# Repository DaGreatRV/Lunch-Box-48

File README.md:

Lunch-Box-48
============

A small Avalon based miner

See the thread on bitcointalk/simple machines forum:
https://bitcointalk.org/index.php?topic=219489.0

Terms of use:
I will not take any responsibility for the use, misuse and/or functionality of the work done in this repository.
You are allowed to use and modify the designs in this repository, please do credit me.
If you modify the design(s), please share them and credit me.
You are allowed to use my designs to build a device for private and/or prototype purposes.
If you would like to use this work for commercial purposes(i.e. manufactor and/or selling it), contact me and we can discuss some form of compensation.

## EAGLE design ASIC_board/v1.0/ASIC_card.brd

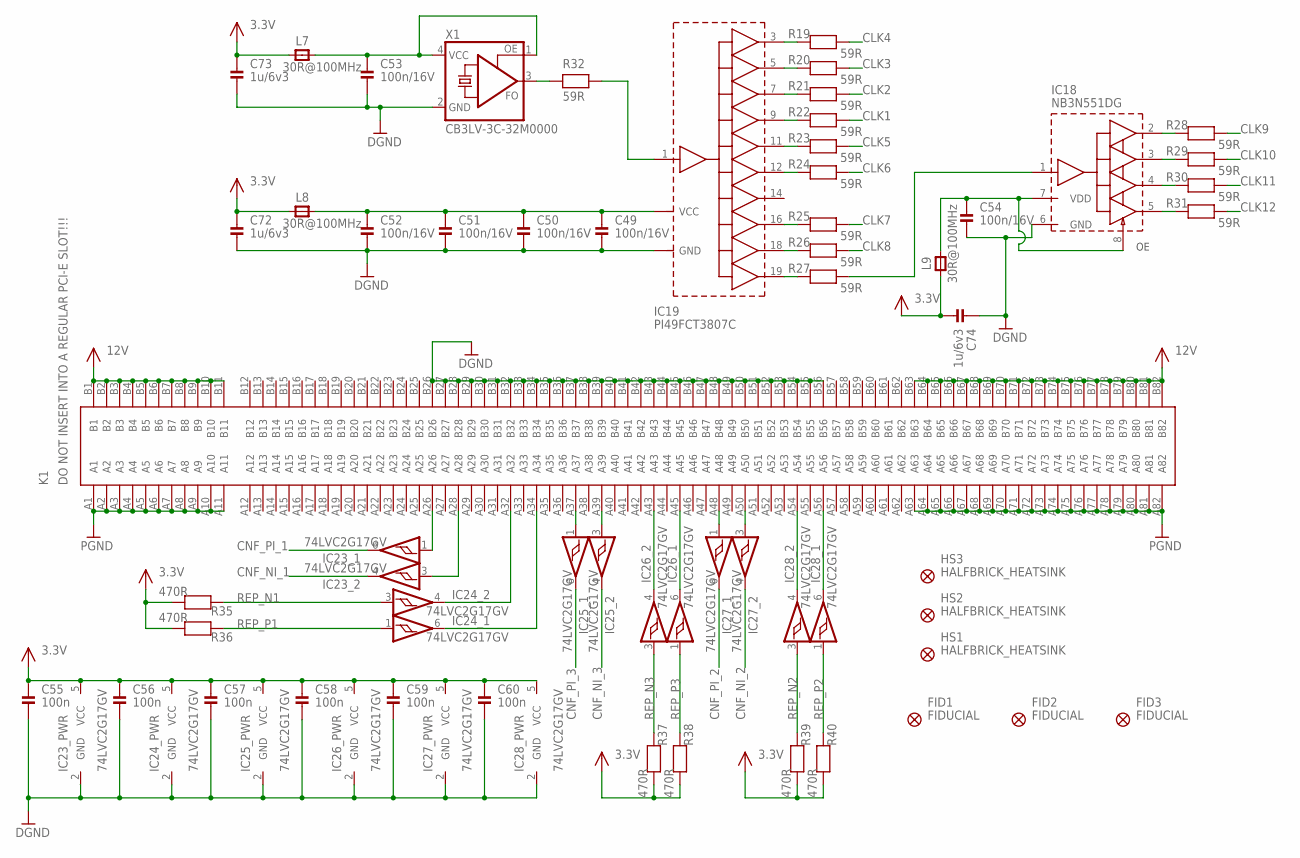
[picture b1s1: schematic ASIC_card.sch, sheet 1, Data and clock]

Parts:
C49, C50, C51, C52, C53, C54: 100n/16V; 0402
C55, C56, C57, C58, C59, C60: 100n; 0603
C72, C73, C74: 1u/6v3; 0402
FID1, FID2, FID3: FIDUCIAL; FID_1X2,5
HS1, HS2, HS3: HALFBRICK_HEATSINK; 1/2_BRICK_HEATSINK
IC18: NB3N551DG; SO-8
IC19: PI49FCT3807C; SSOP-20
IC23, IC24, IC25, IC26, IC27, IC28: 74LVC2G17GV; SOT23-6
K1: DO NOT INSERT INTO A REGULAR PCI-E SLOT!!!; PCI-E_16X
L7, L8, L9: 30R@100MHz; 0603
R19, R20, R21, R22, R23, R24, R25, R26, R27, R28, R29, R30, R31, R32: 59R; 0402
R35, R36, R37, R38, R39, R40: 470R; 0603
X1: CB3LV-3C-32M0000; 7X5_OSC

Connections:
3.3V: C55.1, C56.1, C57.1, C58.1, C59.1, C60.1, C72.1, C73.1, C74.2, IC23.5 (VCC), IC24.5 (VCC), IC25.5 (VCC), IC26.5 (VCC), IC27.5 (VCC), IC28.5 (VCC), L7.1, L8.1, L9.1, R35.1, R36.1, R37.1, R38.1, R39.1, R40.1; also elsewhere on the board
12V: K1.B1, K1.B2, K1.B3, K1.B4, K1.B5, K1.B6, K1.B7, K1.B8, K1.B9, K1.B10, K1.B11, K1.B63, K1.B64, K1.B65, K1.B66, K1.B67, K1.B68, K1.B69, K1.B70, K1.B71, K1.B72, K1.B73, K1.B74, K1.B75, K1.B76, K1.B77, K1.B78, K1.B79, K1.B80, K1.B81, K1.B82; also elsewhere on the board
CLK1: R22.2; also elsewhere on the board
CLK2: R21.2; also elsewhere on the board
CLK3: R20.2; also elsewhere on the board
CLK4: R19.2; also elsewhere on the board
CLK5: R23.2; also elsewhere on the board
CLK6: R24.2; also elsewhere on the board
CLK7: R25.2; also elsewhere on the board
CLK8: R26.2; also elsewhere on the board
CLK9: R28.2; also elsewhere on the board
CLK10: R29.2; also elsewhere on the board
CLK11: R30.2; also elsewhere on the board
CLK12: R31.2; also elsewhere on the board
CNF_NI_1: IC23.4 (O); also elsewhere on the board
CNF_NI_2: IC27.4 (O); also elsewhere on the board
CNF_NI_3: IC25.4 (O); also elsewhere on the board
CNF_PI_1: IC23.6 (O); also elsewhere on the board
CNF_PI_2: IC27.6 (O); also elsewhere on the board
CNF_PI_3: IC25.6 (O); also elsewhere on the board
DGND: C49.2, C50.2, C51.2, C52.2, C53.2, C54.2, C55.2, C56.2, C57.2, C58.2, C59.2, C60.2, C72.2, C73.2, C74.1, IC18.6 (GND), IC19.2 (GND), IC19.6 (GND), IC19.10 (GND), IC19.13 (GND), IC19.17 (GND), IC23.2 (GND), IC24.2 (GND), IC25.2 (GND), IC26.2 (GND), IC27.2 (GND), IC28.2 (GND), K1.B26, K1.B27, K1.B28, K1.B29, K1.B30, K1.B31, K1.B32, K1.B33, K1.B34, K1.B35, K1.B36, K1.B37, K1.B38, K1.B39, K1.B40, K1.B41, K1.B42, K1.B43, K1.B44, K1.B45, K1.B46, K1.B47, K1.B48, K1.B49, K1.B50, K1.B51, K1.B52, K1.B53, K1.B54, K1.B55, K1.B56, X1.2 (GND); also elsewhere on the board
unnamed: IC23.1 (I), K1.A26
unnamed: IC23.3 (I), K1.A28
unnamed: IC19.18 (B8), R26.1
unnamed: IC19.19 (B9), R27.1
unnamed: IC19.16 (B7), R25.1
unnamed: IC19.12 (B5), R24.1
unnamed: IC19.11 (B4), R23.1
unnamed: IC19.9 (B3), R22.1
unnamed: IC19.7 (B2), R21.1
unnamed: IC19.5 (B1), R20.1
unnamed: IC19.3 (B0), R19.1
unnamed: IC18.2 (Q1), R28.1
unnamed: IC18.3 (Q2), R29.1
unnamed: IC18.4 (Q3), R30.1
unnamed: IC18.5 (Q4), R31.1
unnamed: IC24.4 (O), K1.A32
unnamed: IC24.6 (O), K1.A34
unnamed: IC26.6 (O), K1.A45
unnamed: R32.1, X1.3 (FO)
unnamed: IC19.1 (A), R32.2
unnamed: IC26.4 (O), K1.A43
unnamed: IC28.4 (O), K1.A54
unnamed: IC28.6 (O), K1.A56
unnamed: IC27.1 (I), K1.A48
unnamed: IC27.3 (I), K1.A50
unnamed: C53.1, L7.2, X1.1 (OE), X1.4 (VCC)
unnamed: C54.1, IC18.7 (VDD), IC18.8 (OE), L9.2
unnamed: C49.1, C50.1, C51.1, C52.1, IC19.4 (VCC), IC19.8 (VCC), IC19.15 (VCC), IC19.20 (VCC), L8.2
unnamed: IC18.1 (CLK), R27.2
unnamed: IC25.1 (I), K1.A37
unnamed: IC25.3 (I), K1.A39
PGND: K1.A1, K1.A2, K1.A3, K1.A4, K1.A5, K1.A6, K1.A7, K1.A8, K1.A9, K1.A10, K1.A11, K1.A63, K1.A64, K1.A65, K1.A66, K1.A67, K1.A68, K1.A69, K1.A70, K1.A71, K1.A72, K1.A73, K1.A74, K1.A75, K1.A76, K1.A77, K1.A78, K1.A79, K1.A80, K1.A81, K1.A82; also elsewhere on the board
REP_N1: IC24.3 (I), R35.2; also elsewhere on the board
REP_N2: IC28.3 (I), R39.2; also elsewhere on the board
REP_N3: IC26.3 (I), R37.2; also elsewhere on the board
REP_P1: IC24.1 (I), R36.2; also elsewhere on the board
REP_P2: IC28.1 (I), R40.2; also elsewhere on the board
REP_P3: IC26.1 (I), R38.2; also elsewhere on the board

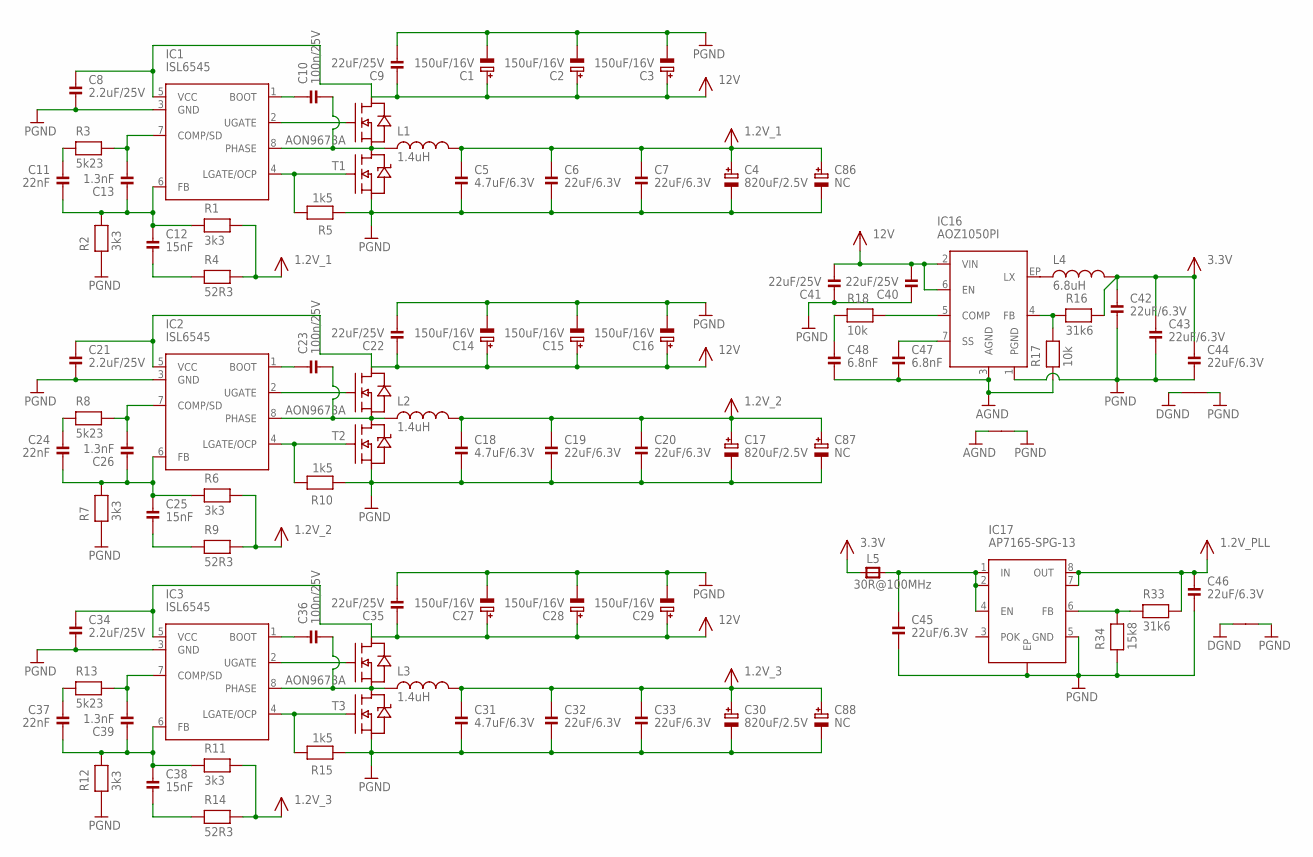
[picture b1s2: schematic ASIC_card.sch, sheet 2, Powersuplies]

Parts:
C1, C2, C3, C14, C15, C16, C27, C28, C29: 150uF/16V; CAP_POL_8MM
C4, C17, C30: 820uF/2.5V; CAP_POL_8MM
C5, C18, C31: 4.7uF/6.3V; 0306
C6, C7, C19, C20, C32, C33, C42, C43, C44, C45, C46: 22uF/6.3V; 0805
C8, C21, C34: 2.2uF/25V; 0603
C9, C22, C35, C40, C41: 22uF/25V; 1210
C10, C23, C36: 100n/25V; 0603
C11, C24, C37: 22nF; 0603
C12, C25, C38: 15nF; 0603
C13, C26, C39: 1.3nF; 0603
C47, C48: 6.8nF; 0603
C86, C87, C88: NC; CAP_POL_8MM
IC1, IC2, IC3: ISL6545; SO-8_BIGPADS
IC16: AOZ1050PI; SO-8_EP
IC17: AP7165-SPG-13; SO-8_EP
L1, L2, L3: 1.4uH; B82559A0142A013
L4: 6.8uH; SRU1048-6R8Y
L5: 30R@100MHz; 0603
R1, R2, R6, R7, R11, R12: 3k3; 0603
R3, R8, R13: 5k23; 0603
R4, R9, R14: 52R3; 0603
R5, R10, R15: 1k5; 0603
R16, R33: 31k6; 0603
R17, R18: 10k; 0603
R34: 15k8; 0603
T1, T2, T3: AON9673A; DFN5X6
VIA1, VIA2, VIA3: VIA

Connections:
1.2V_1: C4.P$1 (+), C5.1, C6.1, C7.1, C86.P$1 (+), L1.2, R1.2, R4.2; also elsewhere on the board
1.2V_2: C17.P$1 (+), C18.1, C19.1, C20.1, C87.P$1 (+), L2.2, R6.2, R9.2; also elsewhere on the board
1.2V_3: C30.P$1 (+), C31.1, C32.1, C33.1, C88.P$1 (+), L3.2, R11.2, R14.2; also elsewhere on the board
1.2V_PLL: C46.1, IC17.7 (OUT1), IC17.8 (OUT), R33.2; also elsewhere on the board
3.3V: C42.1, C43.1, C44.1, L4.2, L5.1, R16.2; also elsewhere on the board
12V: C1.P$1 (+), C2.P$1 (+), C3.P$1 (+), C8.1, C9.1, C14.P$1 (+), C15.P$1 (+), C16.P$1 (+), C21.1, C22.1, C27.P$1 (+), C28.P$1 (+), C29.P$1 (+), C34.1, C35.1, C40.2, C41.2, IC1.5 (VCC), IC2.5 (VCC), IC3.5 (VCC), IC16.2 (VIN), IC16.6 (EN), T1.D1, T2.D1, T3.D1; also elsewhere on the board
AGND: C47.2, C48.2, IC16.3 (AGND), R17.1, VIA1.P$1
DGND: VIA2.P$1, VIA3.P$1; also elsewhere on the board
unnamed: C12.2, R4.1
unnamed: IC1.2 (UGATE), T1.1 (G1)
unnamed: IC1.4 (LGATE/OCP), R5.2, T1.8 (G2)
unnamed: C10.1, IC1.1 (BOOT)
unnamed: C13.2, IC1.7 (COMP/SD), R3.2
unnamed: C11.1, R3.1
unnamed: C11.2, C12.1, C13.1, IC1.6 (FB), R1.1, R2.2
unnamed: C10.2, IC1.8 (PHASE), L1.1, T1.S1_D2
unnamed: IC3.2 (UGATE), T3.1 (G1)
unnamed: IC2.2 (UGATE), T2.1 (G1)
unnamed: IC2.4 (LGATE/OCP), R10.2, T2.8 (G2)
unnamed: C23.2, IC2.8 (PHASE), L2.1, T2.S1_D2
unnamed: C23.1, IC2.1 (BOOT)
unnamed: C26.2, IC2.7 (COMP/SD), R8.2
unnamed: C24.1, R8.1
unnamed: C24.2, C25.1, C26.1, IC2.6 (FB), R6.1, R7.2
unnamed: C25.2, R9.1
unnamed: IC3.4 (LGATE/OCP), R15.2, T3.8 (G2)
unnamed: C36.2, IC3.8 (PHASE), L3.1, T3.S1_D2
unnamed: C36.1, IC3.1 (BOOT)
unnamed: C39.2, IC3.7 (COMP/SD), R13.2
unnamed: C37.1, R13.1
unnamed: C37.2, C38.1, C39.1, IC3.6 (FB), R11.1, R12.2
unnamed: C38.2, R14.1
unnamed: C47.1, IC16.7 (SS)
unnamed: C45.1, IC17.1 (IN), IC17.2 (IN1), IC17.4 (EN), L5.2
unnamed: C48.1, R18.1
unnamed: IC16.5 (COMP), R18.2
unnamed: IC16.4 (FB), R16.1, R17.2
unnamed: IC16.EP (LX), L4.1
unnamed: IC17.6 (FB), R33.1, R34.2
PGND: C1.P$2 (-), C2.P$2 (-), C3.P$2 (-), C4.P$2 (-), C5.2, C6.2, C7.2, C8.2, C9.2, C14.P$2 (-), C15.P$2 (-), C16.P$2 (-), C17.P$2 (-), C18.2, C19.2, C20.2, C21.2, C22.2, C27.P$2 (-), C28.P$2 (-), C29.P$2 (-), C30.P$2 (-), C31.2, C32.2, C33.2, C34.2, C35.2, C40.1, C41.1, C42.2, C43.2, C44.2, C45.2, C46.2, C86.P$2 (-), C87.P$2 (-), C88.P$2 (-), IC1.3 (GND), IC2.3 (GND), IC3.3 (GND), IC16.1 (PGND), IC17.5 (GND), IC17.EP, R2.1, R5.1, R7.1, R10.1, R12.1, R15.1, R34.1, T1.5 (S2), T1.6 (S2), T1.7 (S2), T2.5 (S2), T2.6 (S2), T2.7 (S2), T3.5 (S2), T3.6 (S2), T3.7 (S2), VIA1.P$2, VIA2.P$2, VIA3.P$2; also elsewhere on the board

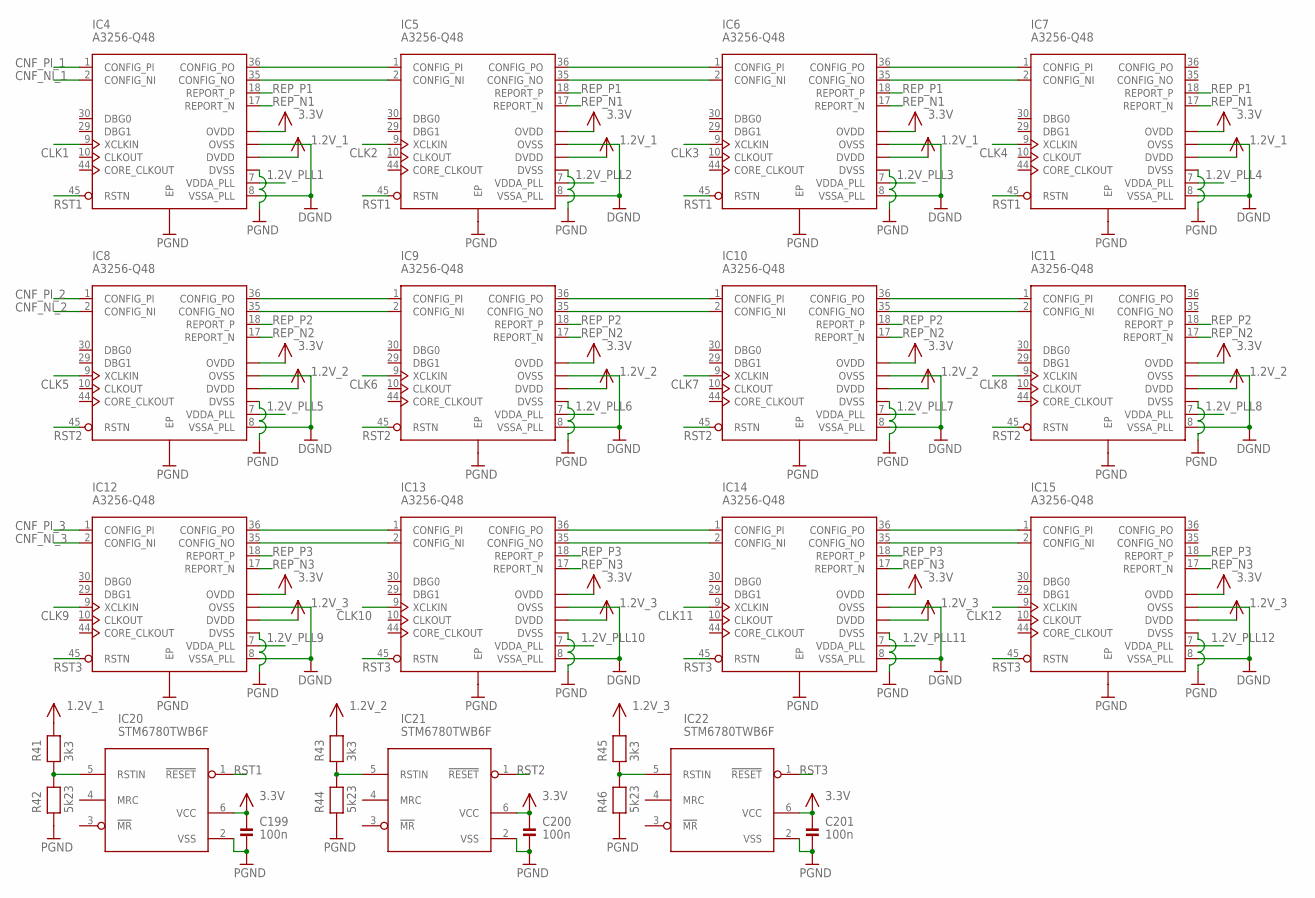
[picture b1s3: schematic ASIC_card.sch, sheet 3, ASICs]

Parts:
C199, C200, C201: 100n; 0603
IC4, IC5, IC6, IC7, IC8, IC9, IC10, IC11, IC12, IC13, IC14, IC15: A3256-Q48; QFN48_EP
IC20, IC21, IC22: STM6780TWB6F; SOT23-6
R41, R43, R45: 3k3; 0603
R42, R44, R46: 5k23; 0603

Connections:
1.2V_1: IC4.3 (DVDD), IC4.4 (DVDD), IC4.6 (DVDD), IC4.11 (DVDD), IC4.12 (DVDD), IC4.13 (DVDD), IC4.14 (DVDD), IC4.15 (DVDD), IC4.16 (DVDD), IC4.19 (DVDD), IC4.21 (DVDD), IC4.22 (DVDD), IC4.25 (DVDD), IC4.26 (DVDD), IC4.27 (DVDD), IC4.28 (DVDD), IC4.31 (DVDD), IC4.33 (DVDD), IC4.34 (DVDD), IC4.39 (DVDD), IC4.40 (DVDD), IC4.41 (DVDD), IC4.43 (DVDD), IC4.46 (DVDD), IC4.47 (DVDD), IC4.48 (DVDD), IC5.3 (DVDD), IC5.4 (DVDD), IC5.6 (DVDD), IC5.11 (DVDD), IC5.12 (DVDD), IC5.13 (DVDD), IC5.14 (DVDD), IC5.15 (DVDD), IC5.16 (DVDD), IC5.19 (DVDD), IC5.21 (DVDD), IC5.22 (DVDD), IC5.25 (DVDD), IC5.26 (DVDD), IC5.27 (DVDD), IC5.28 (DVDD), IC5.31 (DVDD), IC5.33 (DVDD), IC5.34 (DVDD), IC5.39 (DVDD), IC5.40 (DVDD), IC5.41 (DVDD), IC5.43 (DVDD), IC5.46 (DVDD), IC5.47 (DVDD), IC5.48 (DVDD), IC6.3 (DVDD), IC6.4 (DVDD), IC6.6 (DVDD), IC6.11 (DVDD), IC6.12 (DVDD), IC6.13 (DVDD), IC6.14 (DVDD), IC6.15 (DVDD), IC6.16 (DVDD), IC6.19 (DVDD), IC6.21 (DVDD), IC6.22 (DVDD), IC6.25 (DVDD), IC6.26 (DVDD), IC6.27 (DVDD), IC6.28 (DVDD), IC6.31 (DVDD), IC6.33 (DVDD), IC6.34 (DVDD), IC6.39 (DVDD), IC6.40 (DVDD), IC6.41 (DVDD), IC6.43 (DVDD), IC6.46 (DVDD), IC6.47 (DVDD), IC6.48 (DVDD), IC7.3 (DVDD), IC7.4 (DVDD), IC7.6 (DVDD), IC7.11 (DVDD), IC7.12 (DVDD), IC7.13 (DVDD), IC7.14 (DVDD), IC7.15 (DVDD), IC7.16 (DVDD), IC7.19 (DVDD), IC7.21 (DVDD), IC7.22 (DVDD), IC7.25 (DVDD), IC7.26 (DVDD), IC7.27 (DVDD), IC7.28 (DVDD), IC7.31 (DVDD), IC7.33 (DVDD), IC7.34 (DVDD), IC7.39 (DVDD), IC7.40 (DVDD), IC7.41 (DVDD), IC7.43 (DVDD), IC7.46 (DVDD), IC7.47 (DVDD), IC7.48 (DVDD), R41.2; also elsewhere on the board
1.2V_2: IC8.3 (DVDD), IC8.4 (DVDD), IC8.6 (DVDD), IC8.11 (DVDD), IC8.12 (DVDD), IC8.13 (DVDD), IC8.14 (DVDD), IC8.15 (DVDD), IC8.16 (DVDD), IC8.19 (DVDD), IC8.21 (DVDD), IC8.22 (DVDD), IC8.25 (DVDD), IC8.26 (DVDD), IC8.27 (DVDD), IC8.28 (DVDD), IC8.31 (DVDD), IC8.33 (DVDD), IC8.34 (DVDD), IC8.39 (DVDD), IC8.40 (DVDD), IC8.41 (DVDD), IC8.43 (DVDD), IC8.46 (DVDD), IC8.47 (DVDD), IC8.48 (DVDD), IC9.3 (DVDD), IC9.4 (DVDD), IC9.6 (DVDD), IC9.11 (DVDD), IC9.12 (DVDD), IC9.13 (DVDD), IC9.14 (DVDD), IC9.15 (DVDD), IC9.16 (DVDD), IC9.19 (DVDD), IC9.21 (DVDD), IC9.22 (DVDD), IC9.25 (DVDD), IC9.26 (DVDD), IC9.27 (DVDD), IC9.28 (DVDD), IC9.31 (DVDD), IC9.33 (DVDD), IC9.34 (DVDD), IC9.39 (DVDD), IC9.40 (DVDD), IC9.41 (DVDD), IC9.43 (DVDD), IC9.46 (DVDD), IC9.47 (DVDD), IC9.48 (DVDD), IC10.3 (DVDD), IC10.4 (DVDD), IC10.6 (DVDD), IC10.11 (DVDD), IC10.12 (DVDD), IC10.13 (DVDD), IC10.14 (DVDD), IC10.15 (DVDD), IC10.16 (DVDD), IC10.19 (DVDD), IC10.21 (DVDD), IC10.22 (DVDD), IC10.25 (DVDD), IC10.26 (DVDD), IC10.27 (DVDD), IC10.28 (DVDD), IC10.31 (DVDD), IC10.33 (DVDD), IC10.34 (DVDD), IC10.39 (DVDD), IC10.40 (DVDD), IC10.41 (DVDD), IC10.43 (DVDD), IC10.46 (DVDD), IC10.47 (DVDD), IC10.48 (DVDD), IC11.3 (DVDD), IC11.4 (DVDD), IC11.6 (DVDD), IC11.11 (DVDD), IC11.12 (DVDD), IC11.13 (DVDD), IC11.14 (DVDD), IC11.15 (DVDD), IC11.16 (DVDD), IC11.19 (DVDD), IC11.21 (DVDD), IC11.22 (DVDD), IC11.25 (DVDD), IC11.26 (DVDD), IC11.27 (DVDD), IC11.28 (DVDD), IC11.31 (DVDD), IC11.33 (DVDD), IC11.34 (DVDD), IC11.39 (DVDD), IC11.40 (DVDD), IC11.41 (DVDD), IC11.43 (DVDD), IC11.46 (DVDD), IC11.47 (DVDD), IC11.48 (DVDD), R43.2; also elsewhere on the board
1.2V_3: IC12.3 (DVDD), IC12.4 (DVDD), IC12.6 (DVDD), IC12.11 (DVDD), IC12.12 (DVDD), IC12.13 (DVDD), IC12.14 (DVDD), IC12.15 (DVDD), IC12.16 (DVDD), IC12.19 (DVDD), IC12.21 (DVDD), IC12.22 (DVDD), IC12.25 (DVDD), IC12.26 (DVDD), IC12.27 (DVDD), IC12.28 (DVDD), IC12.31 (DVDD), IC12.33 (DVDD), IC12.34 (DVDD), IC12.39 (DVDD), IC12.40 (DVDD), IC12.41 (DVDD), IC12.43 (DVDD), IC12.46 (DVDD), IC12.47 (DVDD), IC12.48 (DVDD), IC13.3 (DVDD), IC13.4 (DVDD), IC13.6 (DVDD), IC13.11 (DVDD), IC13.12 (DVDD), IC13.13 (DVDD), IC13.14 (DVDD), IC13.15 (DVDD), IC13.16 (DVDD), IC13.19 (DVDD), IC13.21 (DVDD), IC13.22 (DVDD), IC13.25 (DVDD), IC13.26 (DVDD), IC13.27 (DVDD), IC13.28 (DVDD), IC13.31 (DVDD), IC13.33 (DVDD), IC13.34 (DVDD), IC13.39 (DVDD), IC13.40 (DVDD), IC13.41 (DVDD), IC13.43 (DVDD), IC13.46 (DVDD), IC13.47 (DVDD), IC13.48 (DVDD), IC14.3 (DVDD), IC14.4 (DVDD), IC14.6 (DVDD), IC14.11 (DVDD), IC14.12 (DVDD), IC14.13 (DVDD), IC14.14 (DVDD), IC14.15 (DVDD), IC14.16 (DVDD), IC14.19 (DVDD), IC14.21 (DVDD), IC14.22 (DVDD), IC14.25 (DVDD), IC14.26 (DVDD), IC14.27 (DVDD), IC14.28 (DVDD), IC14.31 (DVDD), IC14.33 (DVDD), IC14.34 (DVDD), IC14.39 (DVDD), IC14.40 (DVDD), IC14.41 (DVDD), IC14.43 (DVDD), IC14.46 (DVDD), IC14.47 (DVDD), IC14.48 (DVDD), IC15.3 (DVDD), IC15.4 (DVDD), IC15.6 (DVDD), IC15.11 (DVDD), IC15.12 (DVDD), IC15.13 (DVDD), IC15.14 (DVDD), IC15.15 (DVDD), IC15.16 (DVDD), IC15.19 (DVDD), IC15.21 (DVDD), IC15.22 (DVDD), IC15.25 (DVDD), IC15.26 (DVDD), IC15.27 (DVDD), IC15.28 (DVDD), IC15.31 (DVDD), IC15.33 (DVDD), IC15.34 (DVDD), IC15.39 (DVDD), IC15.40 (DVDD), IC15.41 (DVDD), IC15.43 (DVDD), IC15.46 (DVDD), IC15.47 (DVDD), IC15.48 (DVDD), R45.2; also elsewhere on the board
1.2V_PLL1: IC4.7 (VDDA_PLL); also elsewhere on the board
1.2V_PLL2: IC5.7 (VDDA_PLL); also elsewhere on the board
1.2V_PLL3: IC6.7 (VDDA_PLL); also elsewhere on the board
1.2V_PLL4: IC7.7 (VDDA_PLL); also elsewhere on the board
1.2V_PLL5: IC8.7 (VDDA_PLL); also elsewhere on the board
1.2V_PLL6: IC9.7 (VDDA_PLL); also elsewhere on the board
1.2V_PLL7: IC10.7 (VDDA_PLL); also elsewhere on the board
1.2V_PLL8: IC11.7 (VDDA_PLL); also elsewhere on the board
1.2V_PLL9: IC12.7 (VDDA_PLL); also elsewhere on the board
1.2V_PLL10: IC13.7 (VDDA_PLL); also elsewhere on the board
1.2V_PLL11: IC14.7 (VDDA_PLL); also elsewhere on the board
1.2V_PLL12: IC15.7 (VDDA_PLL); also elsewhere on the board
3.3V: C199.1, C200.1, C201.1, IC4.24 (OVDD), IC4.37 (OVDD), IC5.24 (OVDD), IC5.37 (OVDD), IC6.24 (OVDD), IC6.37 (OVDD), IC7.24 (OVDD), IC7.37 (OVDD), IC8.24 (OVDD), IC8.37 (OVDD), IC9.24 (OVDD), IC9.37 (OVDD), IC10.24 (OVDD), IC10.37 (OVDD), IC11.24 (OVDD), IC11.37 (OVDD), IC12.24 (OVDD), IC12.37 (OVDD), IC13.24 (OVDD), IC13.37 (OVDD), IC14.24 (OVDD), IC14.37 (OVDD), IC15.24 (OVDD), IC15.37 (OVDD), IC20.6 (VCC), IC21.6 (VCC), IC22.6 (VCC); also elsewhere on the board
CLK1: IC4.9 (XCLKIN); also elsewhere on the board
CLK2: IC5.9 (XCLKIN); also elsewhere on the board
CLK3: IC6.9 (XCLKIN); also elsewhere on the board
CLK4: IC7.9 (XCLKIN); also elsewhere on the board
CLK5: IC8.9 (XCLKIN); also elsewhere on the board
CLK6: IC9.9 (XCLKIN); also elsewhere on the board
CLK7: IC10.9 (XCLKIN); also elsewhere on the board
CLK8: IC11.9 (XCLKIN); also elsewhere on the board
CLK9: IC12.9 (XCLKIN); also elsewhere on the board
CLK10: IC13.9 (XCLKIN); also elsewhere on the board
CLK11: IC14.9 (XCLKIN); also elsewhere on the board
CLK12: IC15.9 (XCLKIN); also elsewhere on the board
CNF_NI_1: IC4.2 (CONFIG_NI); also elsewhere on the board
CNF_NI_2: IC8.2 (CONFIG_NI); also elsewhere on the board
CNF_NI_3: IC12.2 (CONFIG_NI); also elsewhere on the board
CNF_PI_1: IC4.1 (CONFIG_PI); also elsewhere on the board
CNF_PI_2: IC8.1 (CONFIG_PI); also elsewhere on the board
CNF_PI_3: IC12.1 (CONFIG_PI); also elsewhere on the board
DGND: IC4.8 (VSSA_PLL), IC4.23 (OVSS), IC4.38 (OVSS), IC5.8 (VSSA_PLL), IC5.23 (OVSS), IC5.38 (OVSS), IC6.8 (VSSA_PLL), IC6.23 (OVSS), IC6.38 (OVSS), IC7.8 (VSSA_PLL), IC7.23 (OVSS), IC7.38 (OVSS), IC8.8 (VSSA_PLL), IC8.23 (OVSS), IC8.38 (OVSS), IC9.8 (VSSA_PLL), IC9.23 (OVSS), IC9.38 (OVSS), IC10.8 (VSSA_PLL), IC10.23 (OVSS), IC10.38 (OVSS), IC11.8 (VSSA_PLL), IC11.23 (OVSS), IC11.38 (OVSS), IC12.8 (VSSA_PLL), IC12.23 (OVSS), IC12.38 (OVSS), IC13.8 (VSSA_PLL), IC13.23 (OVSS), IC13.38 (OVSS), IC14.8 (VSSA_PLL), IC14.23 (OVSS), IC14.38 (OVSS), IC15.8 (VSSA_PLL), IC15.23 (OVSS), IC15.38 (OVSS); also elsewhere on the board
unnamed: IC4.36 (CONFIG_PO), IC5.1 (CONFIG_PI)
unnamed: IC4.35 (CONFIG_NO), IC5.2 (CONFIG_NI)
unnamed: IC5.36 (CONFIG_PO), IC6.1 (CONFIG_PI)
unnamed: IC5.35 (CONFIG_NO), IC6.2 (CONFIG_NI)
unnamed: IC6.36 (CONFIG_PO), IC7.1 (CONFIG_PI)
unnamed: IC6.35 (CONFIG_NO), IC7.2 (CONFIG_NI)
unnamed: IC8.36 (CONFIG_PO), IC9.1 (CONFIG_PI)
unnamed: IC8.35 (CONFIG_NO), IC9.2 (CONFIG_NI)
unnamed: IC9.36 (CONFIG_PO), IC10.1 (CONFIG_PI)
unnamed: IC9.35 (CONFIG_NO), IC10.2 (CONFIG_NI)
unnamed: IC10.36 (CONFIG_PO), IC11.1 (CONFIG_PI)
unnamed: IC10.35 (CONFIG_NO), IC11.2 (CONFIG_NI)
unnamed: IC14.36 (CONFIG_PO), IC15.1 (CONFIG_PI)
unnamed: IC14.35 (CONFIG_NO), IC15.2 (CONFIG_NI)
unnamed: IC13.36 (CONFIG_PO), IC14.1 (CONFIG_PI)
unnamed: IC13.35 (CONFIG_NO), IC14.2 (CONFIG_NI)
unnamed: IC12.36 (CONFIG_PO), IC13.1 (CONFIG_PI)
unnamed: IC12.35 (CONFIG_NO), IC13.2 (CONFIG_NI)
unnamed: IC20.5 (RSTIN), R41.1, R42.2
unnamed: IC21.5 (RSTIN), R43.1, R44.2
unnamed: IC22.5 (RSTIN), R45.1, R46.2
PGND: C199.2, C200.2, C201.2, IC4.5 (DVSS), IC4.20 (DVSS), IC4.32 (DVSS), IC4.42 (DVSS), IC4.EP, IC5.5 (DVSS), IC5.20 (DVSS), IC5.32 (DVSS), IC5.42 (DVSS), IC5.EP, IC6.5 (DVSS), IC6.20 (DVSS), IC6.32 (DVSS), IC6.42 (DVSS), IC6.EP, IC7.5 (DVSS), IC7.20 (DVSS), IC7.32 (DVSS), IC7.42 (DVSS), IC7.EP, IC8.5 (DVSS), IC8.20 (DVSS), IC8.32 (DVSS), IC8.42 (DVSS), IC8.EP, IC9.5 (DVSS), IC9.20 (DVSS), IC9.32 (DVSS), IC9.42 (DVSS), IC9.EP, IC10.5 (DVSS), IC10.20 (DVSS), IC10.32 (DVSS), IC10.42 (DVSS), IC10.EP, IC11.5 (DVSS), IC11.20 (DVSS), IC11.32 (DVSS), IC11.42 (DVSS), IC11.EP, IC12.5 (DVSS), IC12.20 (DVSS), IC12.32 (DVSS), IC12.42 (DVSS), IC12.EP, IC13.5 (DVSS), IC13.20 (DVSS), IC13.32 (DVSS), IC13.42 (DVSS), IC13.EP, IC14.5 (DVSS), IC14.20 (DVSS), IC14.32 (DVSS), IC14.42 (DVSS), IC14.EP, IC15.5 (DVSS), IC15.20 (DVSS), IC15.32 (DVSS), IC15.42 (DVSS), IC15.EP, IC20.2 (VSS), IC21.2 (VSS), IC22.2 (VSS), R42.1, R44.1, R46.1; also elsewhere on the board
REP_N1: IC4.17 (REPORT_N), IC5.17 (REPORT_N), IC6.17 (REPORT_N), IC7.17 (REPORT_N); also elsewhere on the board
REP_N2: IC8.17 (REPORT_N), IC9.17 (REPORT_N), IC10.17 (REPORT_N), IC11.17 (REPORT_N); also elsewhere on the board
REP_N3: IC12.17 (REPORT_N), IC13.17 (REPORT_N), IC14.17 (REPORT_N), IC15.17 (REPORT_N); also elsewhere on the board
REP_P1: IC4.18 (REPORT_P), IC5.18 (REPORT_P), IC6.18 (REPORT_P), IC7.18 (REPORT_P); also elsewhere on the board
REP_P2: IC8.18 (REPORT_P), IC9.18 (REPORT_P), IC10.18 (REPORT_P), IC11.18 (REPORT_P); also elsewhere on the board
REP_P3: IC12.18 (REPORT_P), IC13.18 (REPORT_P), IC14.18 (REPORT_P), IC15.18 (REPORT_P); also elsewhere on the board
RST1: IC4.45 (RSTN), IC5.45 (RSTN), IC6.45 (RSTN), IC7.45 (RSTN), IC20.1 (!RESET!)
RST2: IC8.45 (RSTN), IC9.45 (RSTN), IC10.45 (RSTN), IC11.45 (RSTN), IC21.1 (!RESET!)
RST3: IC12.45 (RSTN), IC13.45 (RSTN), IC14.45 (RSTN), IC15.45 (RSTN), IC22.1 (!RESET!)

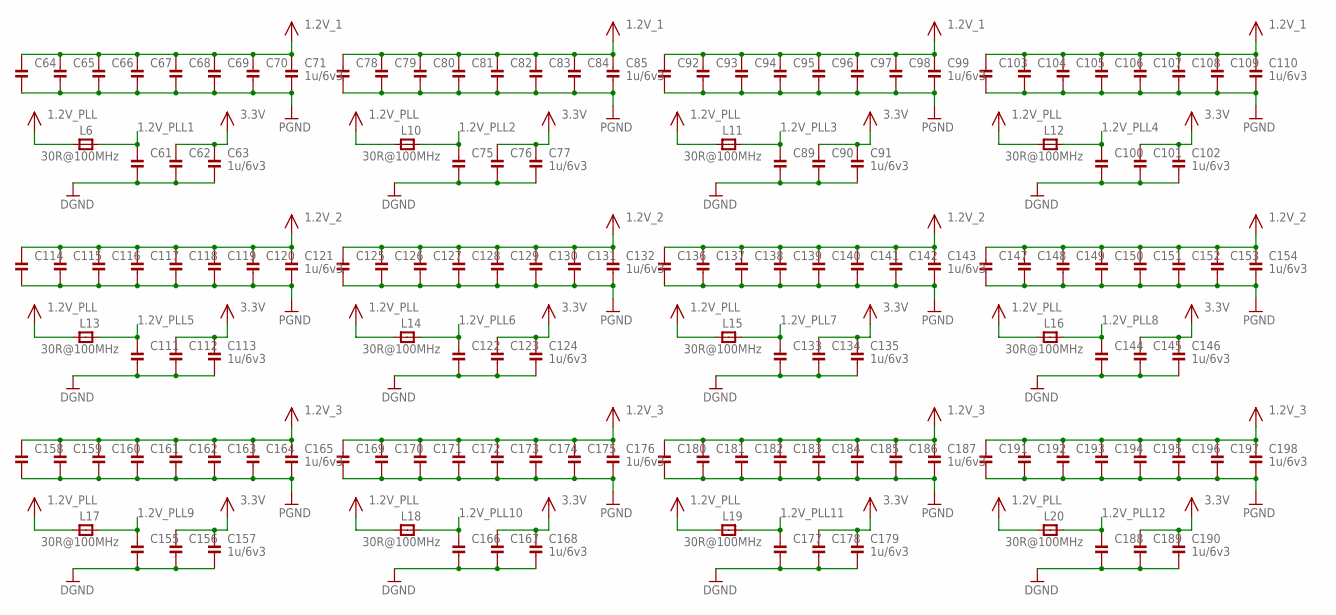
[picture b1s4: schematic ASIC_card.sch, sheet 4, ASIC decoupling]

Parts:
C61, C62, C63, C64, C65, C66, C67, C68, C69, C70, C71, C75, C76, C77, C78, C79, C80, C81, C82, C83, C84, C85, C89, C90, C91, C92, C93, C94, C95, C96, C97, C98, C99, C100, C101, C102, C103, C104, C105, C106, C107, C108, C109, C110, C111, C112, C113, C114, C115, C116, C117, C118, C119, C120, C121, C122, C123, C124, C125, C126, C127, C128, C129, C130, C131, C132, C133, C134, C135, C136, C137, C138, C139, C140, C141, C142, C143, C144, C145, C146, C147, C148, C149, C150, C151, C152, C153, C154, C155, C156, C157, C158, C159, C160, C161, C162, C163, C164, C165, C166, C167, C168, C169, C170, C171, C172, C173, C174, C175, C176, C177, C178, C179, C180, C181, C182, C183, C184, C185, C186, C187, C188, C189, C190, C191, C192, C193, C194, C195, C196, C197, C198: 1u/6v3; 0402
L6, L10, L11, L12, L13, L14, L15, L16, L17, L18, L19, L20: 30R@100MHz; 0603

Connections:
1.2V_1: C64.1, C65.1, C66.1, C67.1, C68.1, C69.1, C70.1, C71.1, C78.1, C79.1, C80.1, C81.1, C82.1, C83.1, C84.1, C85.1, C92.1, C93.1, C94.1, C95.1, C96.1, C97.1, C98.1, C99.1, C103.1, C104.1, C105.1, C106.1, C107.1, C108.1, C109.1, C110.1; also elsewhere on the board
1.2V_2: C114.1, C115.1, C116.1, C117.1, C118.1, C119.1, C120.1, C121.1, C125.1, C126.1, C127.1, C128.1, C129.1, C130.1, C131.1, C132.1, C136.1, C137.1, C138.1, C139.1, C140.1, C141.1, C142.1, C143.1, C147.1, C148.1, C149.1, C150.1, C151.1, C152.1, C153.1, C154.1; also elsewhere on the board
1.2V_3: C158.1, C159.1, C160.1, C161.1, C162.1, C163.1, C164.1, C165.1, C169.1, C170.1, C171.1, C172.1, C173.1, C174.1, C175.1, C176.1, C180.1, C181.1, C182.1, C183.1, C184.1, C185.1, C186.1, C187.1, C191.1, C192.1, C193.1, C194.1, C195.1, C196.1, C197.1, C198.1; also elsewhere on the board
1.2V_PLL: L6.1, L10.1, L11.1, L12.1, L13.1, L14.1, L15.1, L16.1, L17.1, L18.1, L19.1, L20.1; also elsewhere on the board
1.2V_PLL1: C61.1, L6.2; also elsewhere on the board
1.2V_PLL2: C75.1, L10.2; also elsewhere on the board
1.2V_PLL3: C89.1, L11.2; also elsewhere on the board
1.2V_PLL4: C100.1, L12.2; also elsewhere on the board
1.2V_PLL5: C111.1, L13.2; also elsewhere on the board
1.2V_PLL6: C122.1, L14.2; also elsewhere on the board
1.2V_PLL7: C133.1, L15.2; also elsewhere on the board
1.2V_PLL8: C144.1, L16.2; also elsewhere on the board
1.2V_PLL9: C155.1, L17.2; also elsewhere on the board
1.2V_PLL10: C166.1, L18.2; also elsewhere on the board
1.2V_PLL11: C177.1, L19.2; also elsewhere on the board
1.2V_PLL12: C188.1, L20.2; also elsewhere on the board
3.3V: C62.1, C63.1, C76.1, C77.1, C90.1, C91.1, C101.1, C102.1, C112.1, C113.1, C123.1, C124.1, C134.1, C135.1, C145.1, C146.1, C156.1, C157.1, C167.1, C168.1, C178.1, C179.1, C189.1, C190.1; also elsewhere on the board
DGND: C61.2, C62.2, C63.2, C75.2, C76.2, C77.2, C89.2, C90.2, C91.2, C100.2, C101.2, C102.2, C111.2, C112.2, C113.2, C122.2, C123.2, C124.2, C133.2, C134.2, C135.2, C144.2, C145.2, C146.2, C155.2, C156.2, C157.2, C166.2, C167.2, C168.2, C177.2, C178.2, C179.2, C188.2, C189.2, C190.2; also elsewhere on the board
PGND: C64.2, C65.2, C66.2, C67.2, C68.2, C69.2, C70.2, C71.2, C78.2, C79.2, C80.2, C81.2, C82.2, C83.2, C84.2, C85.2, C92.2, C93.2, C94.2, C95.2, C96.2, C97.2, C98.2, C99.2, C103.2, C104.2, C105.2, C106.2, C107.2, C108.2, C109.2, C110.2, C114.2, C115.2, C116.2, C117.2, C118.2, C119.2, C120.2, C121.2, C125.2, C126.2, C127.2, C128.2, C129.2, C130.2, C131.2, C132.2, C136.2, C137.2, C138.2, C139.2, C140.2, C141.2, C142.2, C143.2, C147.2, C148.2, C149.2, C150.2, C151.2, C152.2, C153.2, C154.2, C158.2, C159.2, C160.2, C161.2, C162.2, C163.2, C164.2, C165.2, C169.2, C170.2, C171.2, C172.2, C173.2, C174.2, C175.2, C176.2, C180.2, C181.2, C182.2, C183.2, C184.2, C185.2, C186.2, C187.2, C191.2, C192.2, C193.2, C194.2, C195.2, C196.2, C197.2, C198.2; also elsewhere on the board

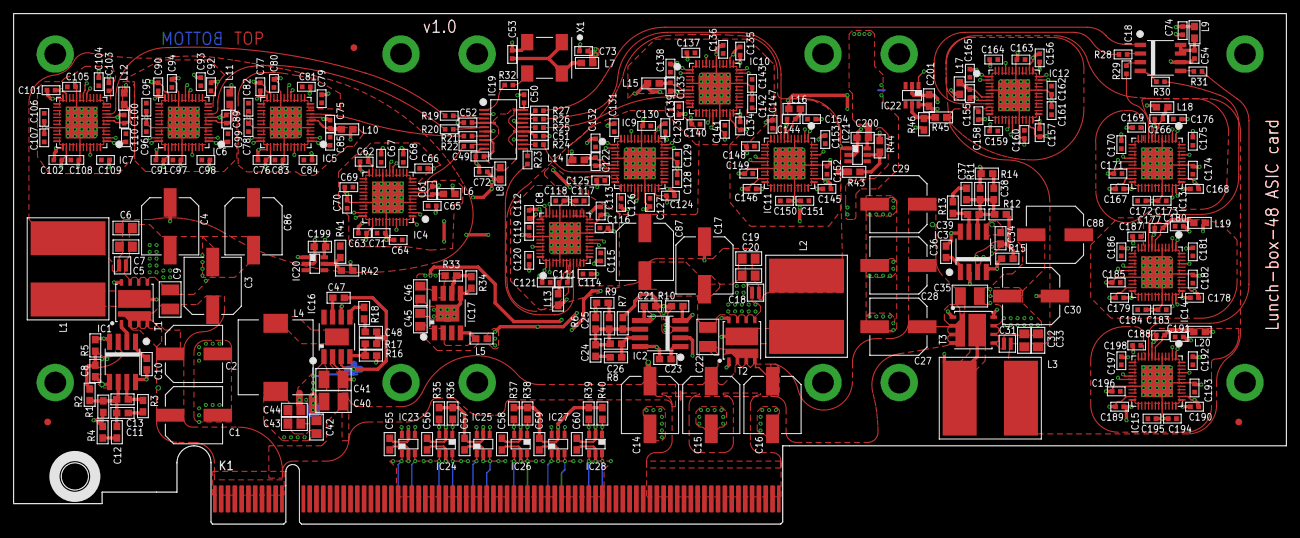
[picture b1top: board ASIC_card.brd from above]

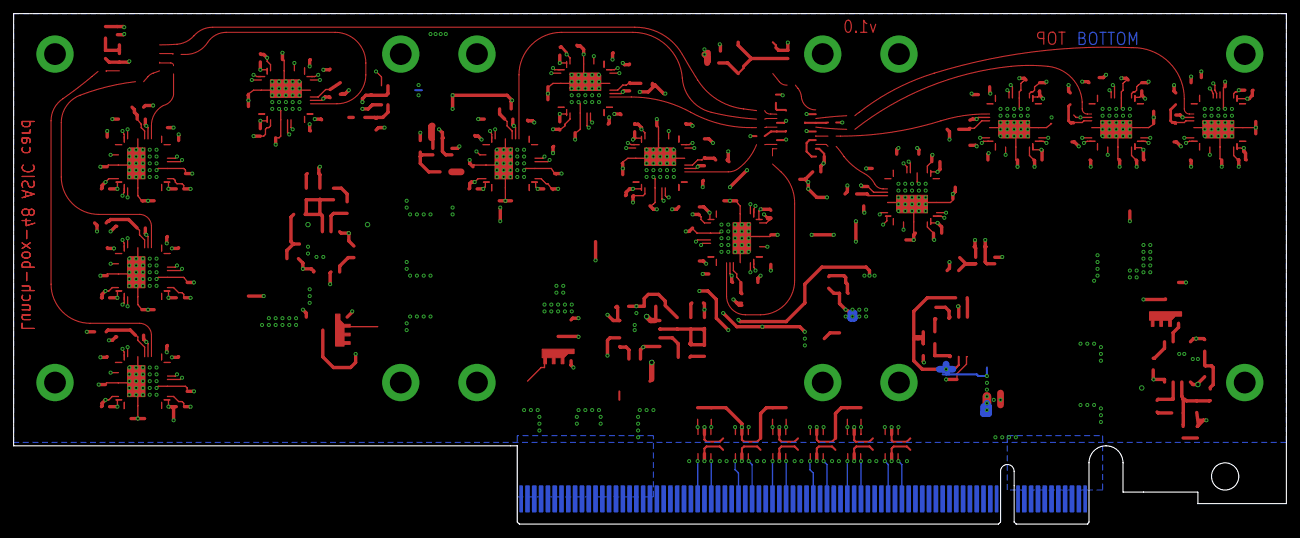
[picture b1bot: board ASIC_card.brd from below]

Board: 4 copper layers, 187.0 x 75.0 mm, 309 parts (3 on the bottom side), 131 nets.

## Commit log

2013-07-17 Update README.md
    added terms of use
2013-07-17 Asic card library added
    I added an Eagle 6 library which contains all of the symbols and
    packages of the Asic board design.
2013-07-17 Made a seperate folder for the ASIC card design
2013-08-01 Updated the PCI-e 16x component
    also I added some screenshots
2013-09-03 Added v1 production files
